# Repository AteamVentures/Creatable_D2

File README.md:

# Creatable D2
Creatable D2는 Reprep기반의 델타방식의 3D프린터입니다.

폴더 설명

 - Hardware : 회도로 및 PCB 파일 (Mainboard는 Cadence의 Allegro로 작업이되어 있고 나머지는 Eagle CAD로 작업)
 - Firmware : 메인 보드 ATmega2560 firmware
 - 16U2 : 메인 보드 Atmega16U2 firmware
 - stk500v2 : 메인 보드 ATmega2560 bootloader

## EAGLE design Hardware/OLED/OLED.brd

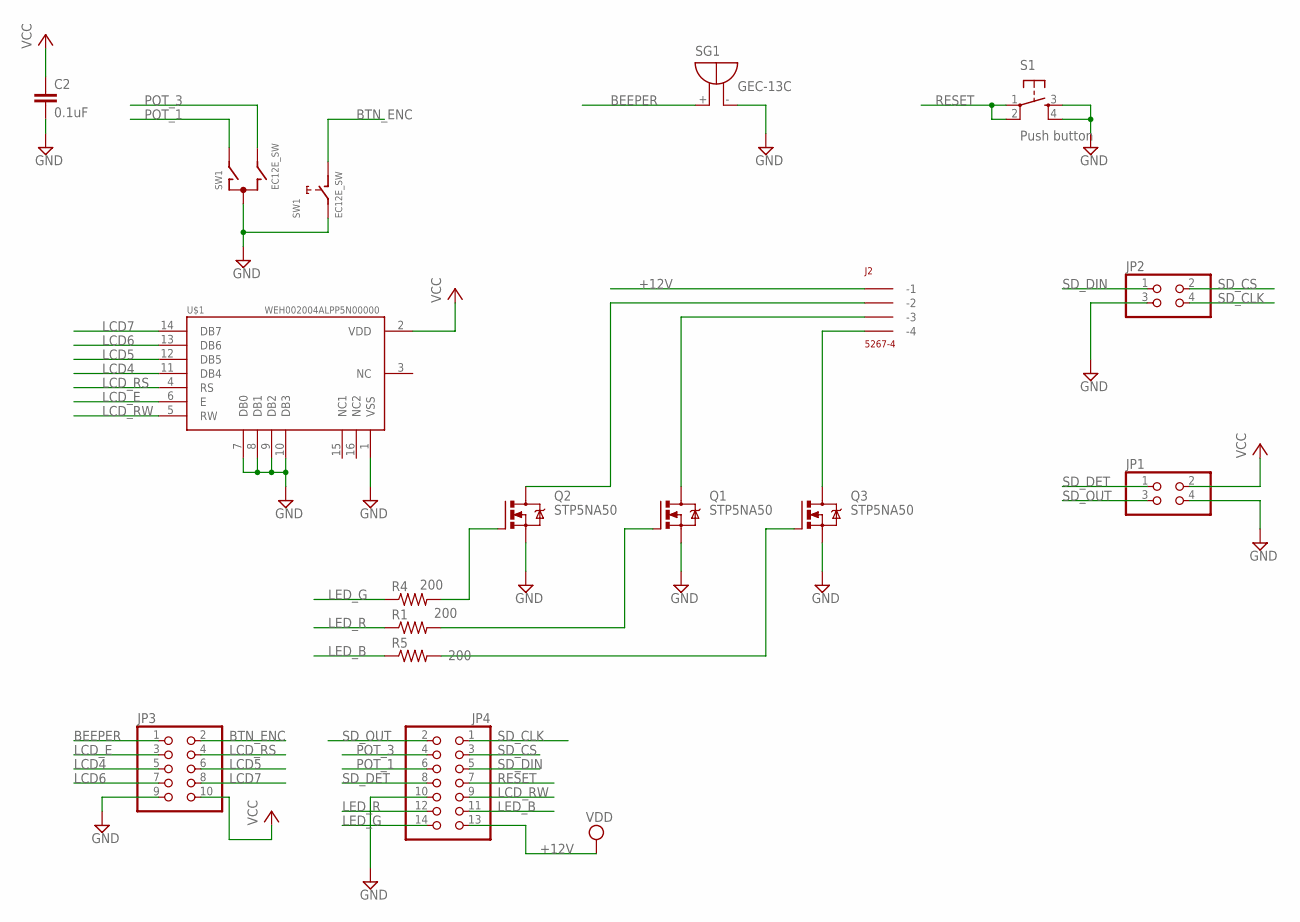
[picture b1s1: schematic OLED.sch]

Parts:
C2: 0.1uF; C0805
J2: 5267-4
JP1, JP2: PINHD-2X2; 2X02
JP3: PINHD-2X5/90; 2X05/90
JP4: PINHD-2X7/90; 2X07/90
Q1, Q2, Q3: STP5NA50; TO220BV
R1, R4, R5: 200; R2012
S1: Push button; TACTILE-PTH
SG1: GEC-13C; F/TMB
SW1: EC12E_SW; ALPS_EC12E_SW
U$1: OLED; WEH002004ALPP5N00000

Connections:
+12V: J2.P$1 (-1), JP4.13
BEEPER: JP3.1, SG1.+
BTN_ENC: JP3.2, SW1.D (1)
GND: C2.2, JP1.4, JP2.3, JP3.9, JP4.10, Q1.S, Q2.S, Q3.S, S1.3, S1.4, SG1.-, SW1.C, SW1.E (2), U$1.1 (VSS), U$1.7 (DB0), U$1.8 (DB1), U$1.9 (DB2), U$1.10 (DB3)
LCD4: JP3.5, U$1.11 (DB4)
LCD5: JP3.6, U$1.12 (DB5)
LCD6: JP3.7, U$1.13 (DB6)
LCD7: JP3.8, U$1.14 (DB7)
LCD_E: JP3.3, U$1.6 (E)
LCD_RS: JP3.4, U$1.4 (RS)
LCD_RW: JP4.9, U$1.5 (RW)
LED_B: JP4.11, R5.1
LED_G: JP4.14, R4.1
LED_R: JP4.12, R1.1
unnamed: Q2.G, R4.2
unnamed: Q1.G, R1.2
unnamed: Q3.G, R5.2
unnamed: J2.P$2 (-2), Q2.D
unnamed: J2.P$3 (-3), Q1.D
unnamed: J2.P$4 (-4), Q3.D
POT_1: JP4.6, SW1.A
POT_3: JP4.4, SW1.B
RESET: JP4.7, S1.1, S1.2
SD_CLK: JP2.4, JP4.1
SD_CS: JP2.2, JP4.3
SD_DET: JP1.1, JP4.8
SD_DIN: JP2.1, JP4.5
SD_OUT: JP1.3, JP4.2
VCC: C2.1, JP1.2, JP3.10, U$1.2 (VDD)

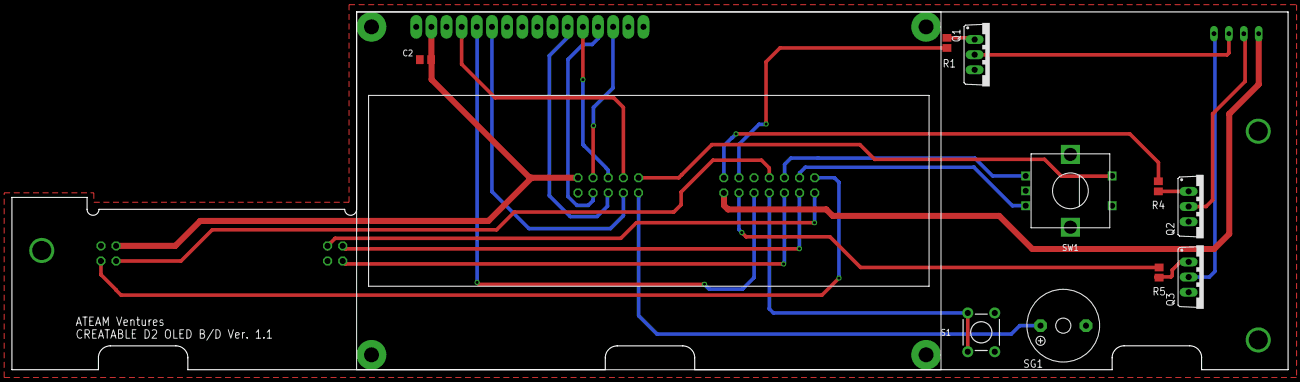
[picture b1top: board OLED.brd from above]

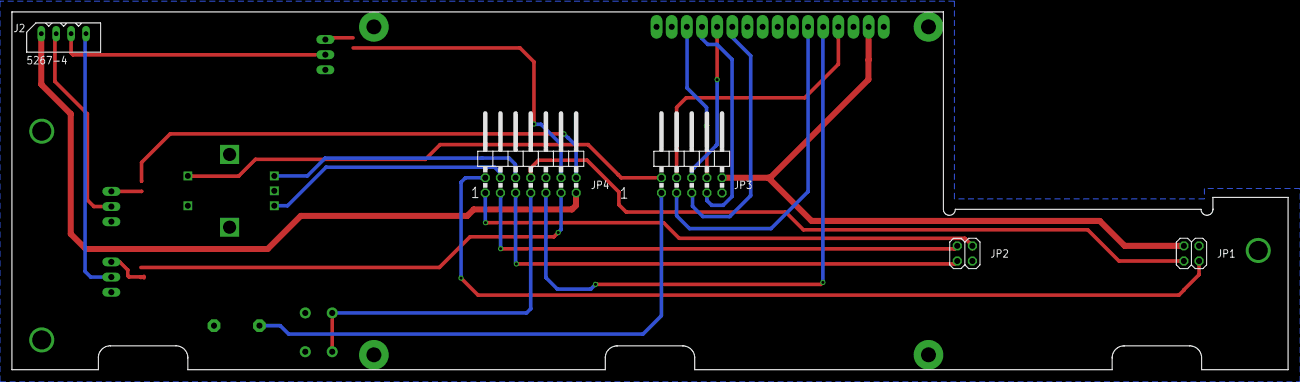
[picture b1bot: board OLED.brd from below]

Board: 2 copper layers, 214.0 x 60.0 mm, 16 parts (5 on the bottom side), 29 nets.

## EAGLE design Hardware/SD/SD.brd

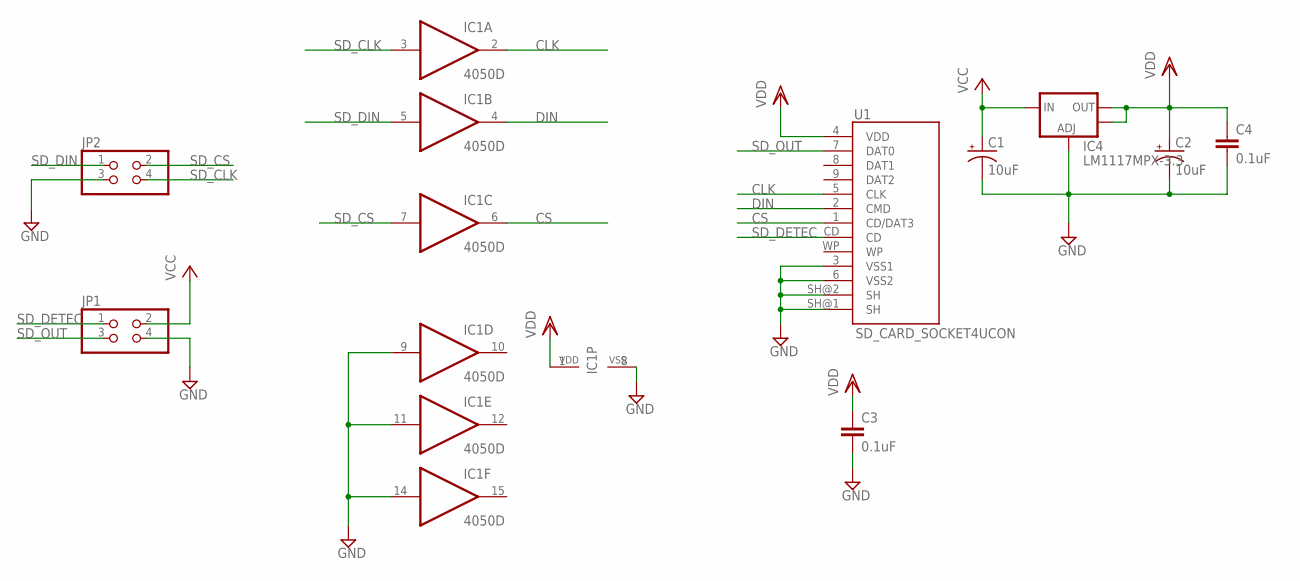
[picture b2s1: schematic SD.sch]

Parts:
C1, C2: 10uF; CT3216
C3, C4: 0.1uF; C0805
IC1: 4050D; SO16
IC4: LM1117MPX-3.3; SOT223
JP1, JP2: PINHD-2X2; 2X02
U1: SD_CARD_SOCKET4UCON; SDCARD_4UCONN

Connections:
CLK: IC1.2 (O), U1.5 (CLK)
CS: IC1.6 (O), U1.1 (CD/DAT3)
DIN: IC1.4 (O), U1.2 (CMD)
GND: C1.-, C2.-, C3.2, C4.2, IC1.8 (VSS), IC1.9 (I), IC1.11 (I), IC1.14 (I), IC4.1 (ADJ), JP1.4, JP2.3, U1.3 (VSS1), U1.6 (VSS2), U1.SH@1 (SH), U1.SH@2 (SH)
SD_CLK: IC1.3 (I), JP2.4
SD_CS: IC1.7 (I), JP2.2
SD_DETEC: JP1.1, U1.CD
SD_DIN: IC1.5 (I), JP2.1
SD_OUT: JP1.3, U1.7 (DAT0)
VCC: C1.+, IC4.3 (IN), JP1.2
VDD: C2.+, C3.1, C4.1, IC1.1 (VDD), IC4.2 (OUT), IC4.4 (OUT), U1.4 (VDD)

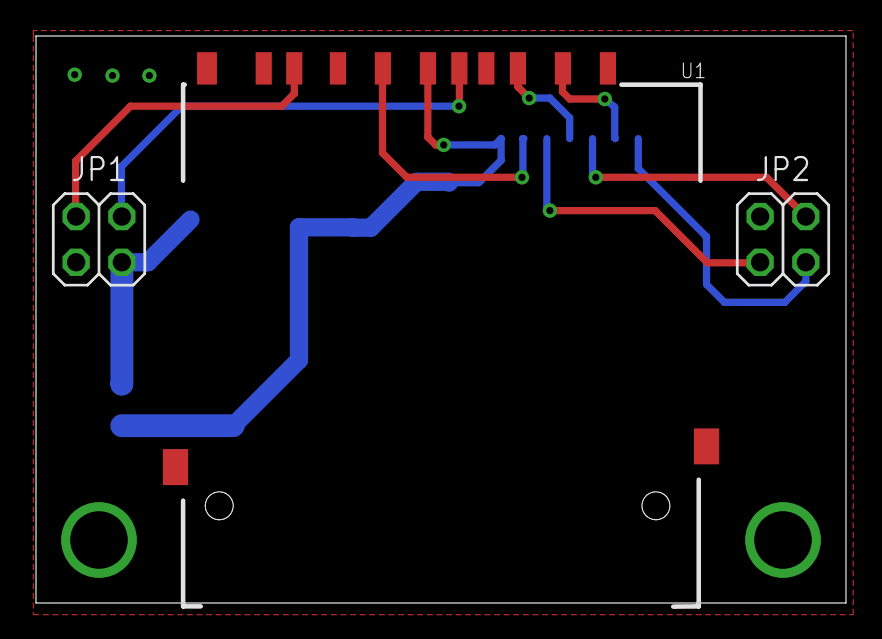
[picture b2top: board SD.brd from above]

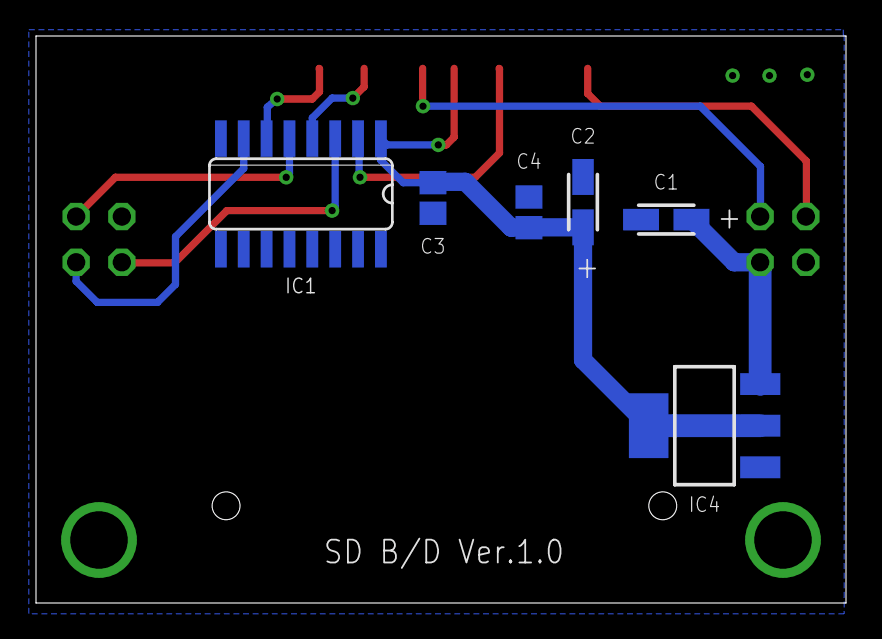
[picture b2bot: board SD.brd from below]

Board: 2 copper layers, 45.0 x 31.5 mm, 9 parts (6 on the bottom side), 11 nets.

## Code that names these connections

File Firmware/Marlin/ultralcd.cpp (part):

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
#ifdef LED_STRIP
    // setup LED Strip
    pinMode(LED_R, OUTPUT);
    pinMode(LED_G, OUTPUT);
    pinMode(LED_B, OUTPUT);
#endif    

#ifdef NEWPANEL
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    WRITE(BTN_EN1,HIGH);
    WRITE(BTN_EN2,HIGH);
  #if BTN_ENC > 0
    pinMode(BTN_ENC,INPUT);
    WRITE(BTN_ENC,HIGH);
  #endif
  #ifdef REPRAPWORLD_KEYPAD
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
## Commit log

2016-01-15 1.0.4
2016-01-15 ver.1.0.5
2016-01-15 Fix filament load & unload bug

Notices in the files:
parts and their libraries:
SparkFun: Licensing: CC v3.0 Share-Alike You are welcome to use this library for commercial purposes.
SparkFun-Connectors: Licensing: Creative Commons ShareAlike 4.0 International - https://creativecommons.org/licenses/by-sa/4.0
